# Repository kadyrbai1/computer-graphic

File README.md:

<h1 align="center"><b>IO Watch</b></h3>

## ⌨️ Collaborators
- Kadyrbai Aitbaev
- Nasip Salmakhunov

## 🔗 Usefull links
- [Thingiverse](https://www.thingiverse.com/thing:4365258/files)

## Device Requirements
<h3>An overview of what components and tools were used in this build.</h3>

 - Microcontroller
  <p>The IC on this board is the ATMega328. </p>
  
 - Power system
  <p>The watch has a battery holder for a 3V, 20mm coin cell battery. Recommended 250mAh at 3V. </p>
  
 - Keeping the time
  <p>Size 0603 RED led's coupled with fairly high value (680 Ohm) resistors keeping the current low and still visible in direct sunlight. </p>
  
 - User interface
  <p>he finest RTC I can get is DS3231 keeping the time precise as it gets.  </p>

## PCB - Schematics and Layout

#### PCB specifications

- Layers:2
- Dimension:35mm*35mm
- Thickness:0.8
- Impedance: no
- PCB Color: Black
- Surface Finish: HASL(with lead)
- Copper Weight:1 oz
- Gold Fingers: No
- Material Details: FR4-Standard Tg 130-140C
- Panel By JLCPCB: No
- Flying Probe Test: Fully
- Test Castellated Holes: no

## Programming
<p>Using the FTDI test (connection) pads provided on the back of the PCB you can use a cheap FTDI converter to upload the code.</p>

## 3D Modeling and Printing
<p>verything except wrist watch band and glass - 3D prints, That includes

- Main body
- Outer Glass ring
- Bottom body
- Buttons
I used the following settings in Cura for my prints:

- 3D Printer - Prusa I3 MK3S
- Material: PLA
- Layer Height - 0.1 mm
- Shell Thickness - 0.8 mm (Nozzle: 0.4 - 2 Shells)
- Top and Bottom Thickness - 0.8mm
- Fill Density - 100%
- Filament - 1.75mm
- Support Type - Everywhere
- Platform adhesion Type - Skirt</p>

## Circuit

## Product

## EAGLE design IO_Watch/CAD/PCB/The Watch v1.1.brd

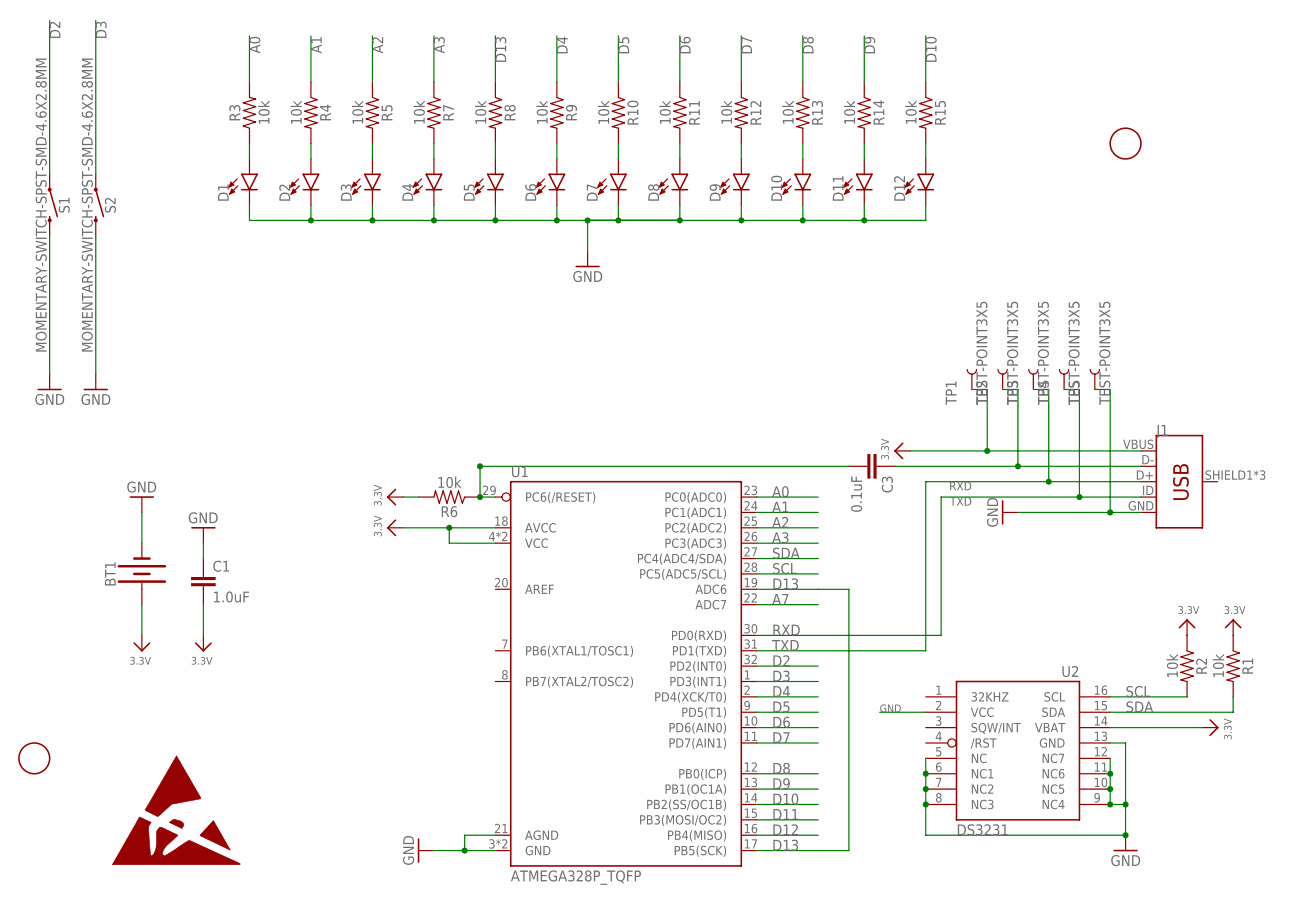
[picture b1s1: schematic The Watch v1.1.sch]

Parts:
BT1: BATTERY-20MM_SMD_4LEGS_OVERPASTE; BATTCON_20MM_4LEGS_OVERPASTE
C1: 1.0uF; 0603
C3: 0.1uF; 0603
D1, D2, D3, D4, D5, D6, D7, D8, D9, D10, D11, D12: LED0603; LED-0603
J1: USB_MICRO-B_FEMALE-SMT; USB-B-MICRO-SMD
R1, R2, R3, R4, R5, R6, R7, R8, R9, R10, R11, R12, R13, R14, R15: 10k; 0603
S1, S2: MOMENTARY-SWITCH-SPST-SMD-4.6X2.8MM; TACTILE_SWITCH_SMD_4.6X2.8MM
TP1, TP2, TP3, TP4, TP5: TEST-POINT3X5; PAD.03X.05
U1: ATMEGA328P_TQFP; TQFP32-08
U2: DS3231/SO; SO16W
U$1, U$10: FIDUCIAL; FIDUCIAL_1MM

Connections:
3.3V: BT1.1 (+), C1.2, J1.VBUS, R1.1, R2.1, R6.2, TP1.P$1, U1.4 (VCC), U1.6 (VCC), U1.18 (AVCC), U2.14 (VBAT)
A0: R3.2, U1.23 (PC0(ADC0))
A1: R4.1, U1.24 (PC1(ADC1))
A2: R5.1, U1.25 (PC2(ADC2))
A3: R7.1, U1.26 (PC3(ADC3))
A7: U1.22 (ADC7)
D2: S1.1, S1.2 (1), U1.32 (PD2(INT0))
D3: S2.1, S2.2 (1), U1.1 (PD3(INT1))
D4: R9.1, U1.2 (PD4(XCK/T0))
D5: R10.1, U1.9 (PD5(T1))
D6: R11.1, U1.10 (PD6(AIN0))
D7: R12.1, U1.11 (PD7(AIN1))
D8: R13.1, U1.12 (PB0(ICP))
D9: R14.1, U1.13 (PB1(OC1A))
D10: R15.1, U1.14 (PB2(SS/OC1B))
D11: U1.15 (PB3(MOSI/OC2))
D12: U1.16 (PB4(MISO))
D13: R8.1, U1.17 (PB5(SCK)), U1.19 (ADC6)
GND: BT1.2 (-), C1.1, D1.C, D2.C, D3.C, D4.C, D5.C, D6.C, D7.C, D8.C, D9.C, D10.C, D11.C, D12.C, J1.GND, S1.3 (2), S1.4 (2), S2.3 (2), S2.4 (2), TP5.P$1, U1.3 (GND), U1.5 (GND), U1.21 (AGND), U2.2 (VCC), U2.5 (NC), U2.6 (NC1), U2.7 (NC2), U2.8 (NC3), U2.9 (NC4), U2.10 (NC5), U2.11 (NC6), U2.12 (NC7), U2.13 (GND)
unnamed: D1.A, R3.1
unnamed: D2.A, R4.2
unnamed: D3.A, R5.2
unnamed: D4.A, R7.2
unnamed: D5.A, R8.2
unnamed: D6.A, R9.2
unnamed: D7.A, R10.2
unnamed: D8.A, R11.2
unnamed: D9.A, R12.2
unnamed: D10.A, R13.2
unnamed: D11.A, R14.2
unnamed: D12.A, R15.2
unnamed: C3.1, J1.D-, TP2.P$1
RESET: C3.2, R6.1, U1.29 (PC6(/RESET))
RXD: J1.ID, TP4.P$1, U1.30 (PD0(RXD))
SCL: R2.2, U1.28 (PC5(ADC5/SCL)), U2.16 (SCL)
SDA: R1.2, U1.27 (PC4(ADC4/SDA)), U2.15 (SDA)
TXD: J1.D+, TP3.P$1, U1.31 (PD1(TXD))

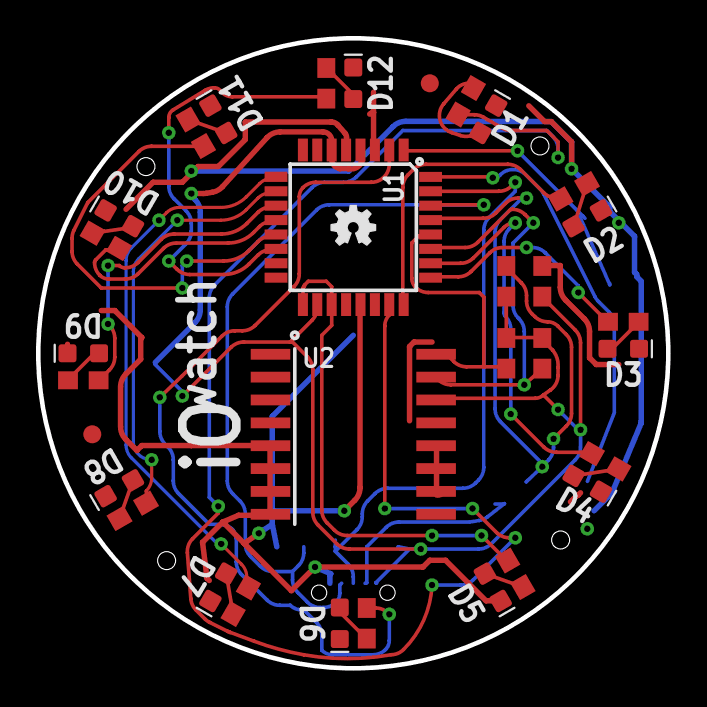
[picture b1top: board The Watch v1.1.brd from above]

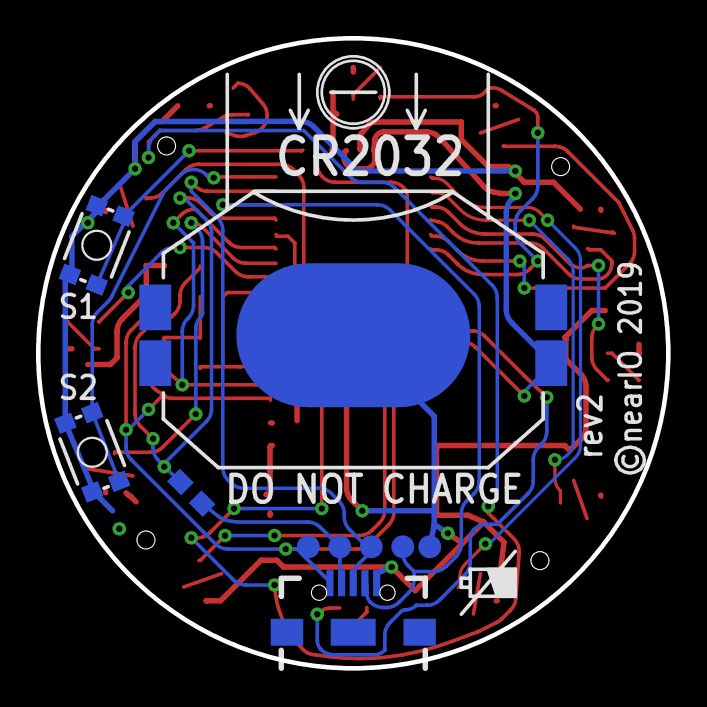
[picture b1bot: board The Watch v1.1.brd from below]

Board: 2 copper layers, 35.0 x 35.0 mm, 43 parts (10 on the bottom side), 34 nets.

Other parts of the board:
U$6: OSHW-LOGO-MINI

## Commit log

2020-05-14 Body stl
2020-05-14 Bottom stl
2020-05-14 Code
2020-05-14 Refactoring
2020-05-14 scad files
2020-05-16 New images

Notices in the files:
IO_Watch/CAD/PCB/The Watch v1.1.brd:
©nearIO 2019
parts and their libraries:
SparkFun-LED: Licensing: Creative Commons ShareAlike 4.0 International - https://creativecommons.org/licenses/by-sa/4.0
microbuilder: This work is placed in the public domain, and may be freely used for commercial and non-commercial work with the following conditions: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
